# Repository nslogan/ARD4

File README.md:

# ARD4

## Description

Optically-isolated 4-channel automotive relay driver (ARD). Intended for use in lab environment, robust and flexible driver with 1A output possible per channel. Jumper to select between active-high and active-low inputs, jumper to select between DB9 or external power for input side. Reverse-protection on both logic and relay side power. LED across relay driver output indicates if **relay** is getting power. Test points for logic and relay power, as well as one per channel on logic side. Board fits Sick of Beige DP8049 form factor (but should be used with 10mm stand-offs between board and top panel). You can find [this project on GitHub](https://github.com/nslogan/ARD4).

## Production

The board measures 3.15"x1.93" (80.01x49.02 mm) and was designed for production at [OSH Park](https://www.oshpark.com/). The OSHPark DRU is located in the `res/` folder.

The boards can be purchased [here](https://www.oshpark.com/shared_projects/R0TELkwq) @ $30.35 for three.

## Parts

All parts on this board are from the [LoganSmith-Eagle-Library](https://github.com/nslogan/LoganSmith-Eagle-Library) available on GitHub (work in progress).

The BOM is located in the release folder, all parts are sourced from Digi-Key.

## Project Structure

This project adheres to this structure:

	[ProjectName]
		README.md
		[release]
			[Major.Minor]
				ProjectName_BOM_Major.Minor.xls or ProjectName_BOM_BOM_Major.Minor.csv
				ProjectName_schematic_Major.Minor.pdf
				ProjectName_board-<top/mid#/bottom>_Major.Minor.png
				ProjectName_Major.Minor.sch
				ProjectName_Major.Minor.brd
				[Gerbers]
					...
			...
		[src]
			[Major.0]
				BoardName.sch
				BoardName.brd
				BOM.xls or BOM.csv
			[Major+1.0]
				...
			...
		[lib]
			...
		[res]
			Manufacturer.dru
			Manufacturer.cam

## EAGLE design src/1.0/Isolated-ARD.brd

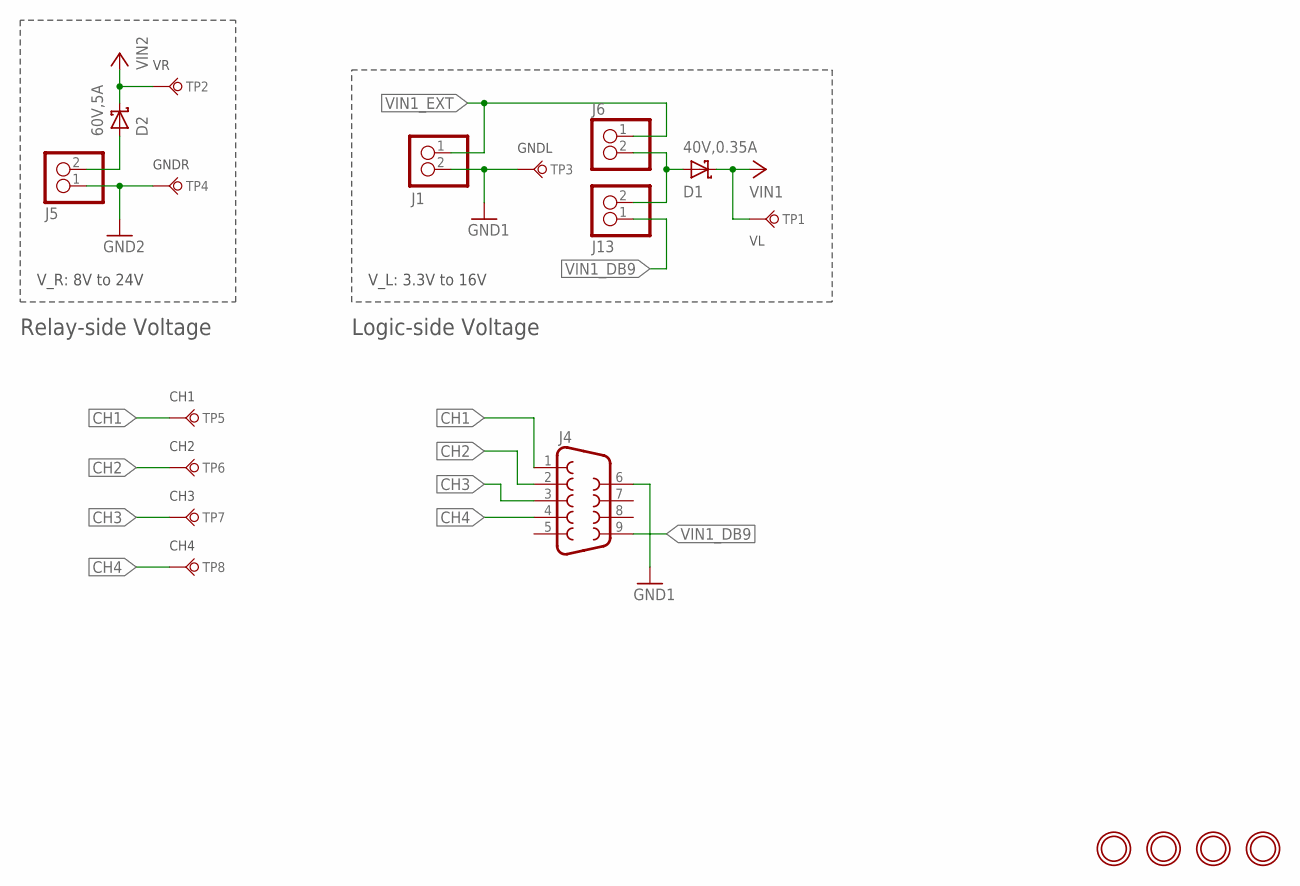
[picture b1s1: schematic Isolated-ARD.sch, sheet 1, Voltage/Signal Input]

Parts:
D1: 40V,0.35A; SOD-323
D2: 60V,5A; SMC-DIODE
J1, J5: M02SKT-3.5MM-R90; SOCKET-3.5MM-2-R90
J4: DB9-R90-F; DB9-R90
J6, J13: M02SQ1; 1X02_SQ1
TP1, TP2: TP-THRU-R; TP_THRU_CIRC
TP3, TP4, TP5, TP6, TP7, TP8: TP-THRU-B; TP_THRU_CIRC
U$13, U$14, U$15, U$21: MNTHOLE-M3; MNTHOLE_M3_PLATED

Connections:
CH1: J4.1, TP5.TP; also elsewhere on the board
CH2: J4.2, TP6.TP; also elsewhere on the board
CH3: J4.3, TP7.TP; also elsewhere on the board
CH4: J4.4, TP8.TP; also elsewhere on the board
GND1: J1.2, J4.6, TP3.TP; also elsewhere on the board
GND2: J5.1, TP4.TP; also elsewhere on the board
unnamed: D1.A, J6.2, J13.2
VIN1: D1.C, TP1.TP; also elsewhere on the board
VIN1_DB9: J4.9, J13.1
VIN1_EXT: J1.1, J6.1
VIN2: D2.C, TP2.TP; also elsewhere on the board
VIN2_EXT: D2.A, J5.2

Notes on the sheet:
V_L: 3.3V to 16V
V_R: 8V to 24V
Logic-side Voltage
Relay-side Voltage

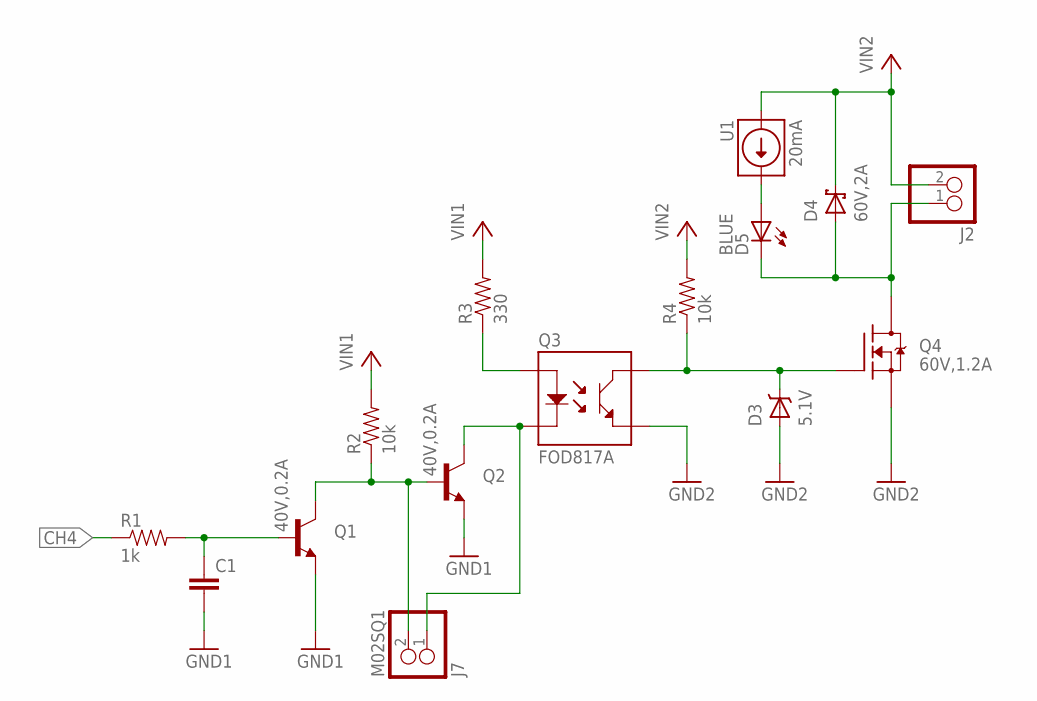
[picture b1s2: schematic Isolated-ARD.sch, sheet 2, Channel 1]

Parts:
C1: C-0805; 0805-CAP
D3: 5.1V; SOD-123
D4: 60V,2A; SMA-DIODE
D5: BLUE; 1206-LED; MPN LTST-C150KBKT; DIGIKEY_OC 160-1643-1-ND
J2: M02SKT-3.5MM-R90; SOCKET-3.5MM-2-R90
J7: M02SQ1; 1X02_SQ1
Q1, Q2: 40V,0.2A; SOT23-3
Q3: FOD817A; 4-SMD
Q4: 60V,1.2A; SOT23-3
R1: 1k; 0805-RES
R2: 10k; 0805-RES
R3: 330; 0805-RES
R4: 10k; 0805-RES; MPN ERJ-6GEYJ103V; DIGIKEY_OC P10KACT-ND
U1: 20mA; SOD-123

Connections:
CH4: R1.P$1 (1); also elsewhere on the board
GND1: C1.P$2 (2), Q1.2 (E), Q2.2 (E); also elsewhere on the board
GND2: D3.A, Q3.3 (T_E), Q4.2 (S); also elsewhere on the board
unnamed: J7.2, Q1.3 (C), Q2.1 (B), R2.P$1 (1)
unnamed: J7.1, Q2.3 (C), Q3.2 (LED_C)
unnamed: Q3.1 (LED_A), R3.P$1 (1)
unnamed: C1.P$1 (1), Q1.1 (B), R1.P$2 (2)
unnamed: D3.C, Q3.4 (T_C), Q4.1 (G), R4.P$1 (1)
unnamed: D4.A, D5.C, J2.1, Q4.3 (D)
unnamed: D5.A, U1.C
VIN1: R2.P$2 (2), R3.P$2 (2); also elsewhere on the board
VIN2: D4.C, J2.2, R4.P$2 (2), U1.A; also elsewhere on the board

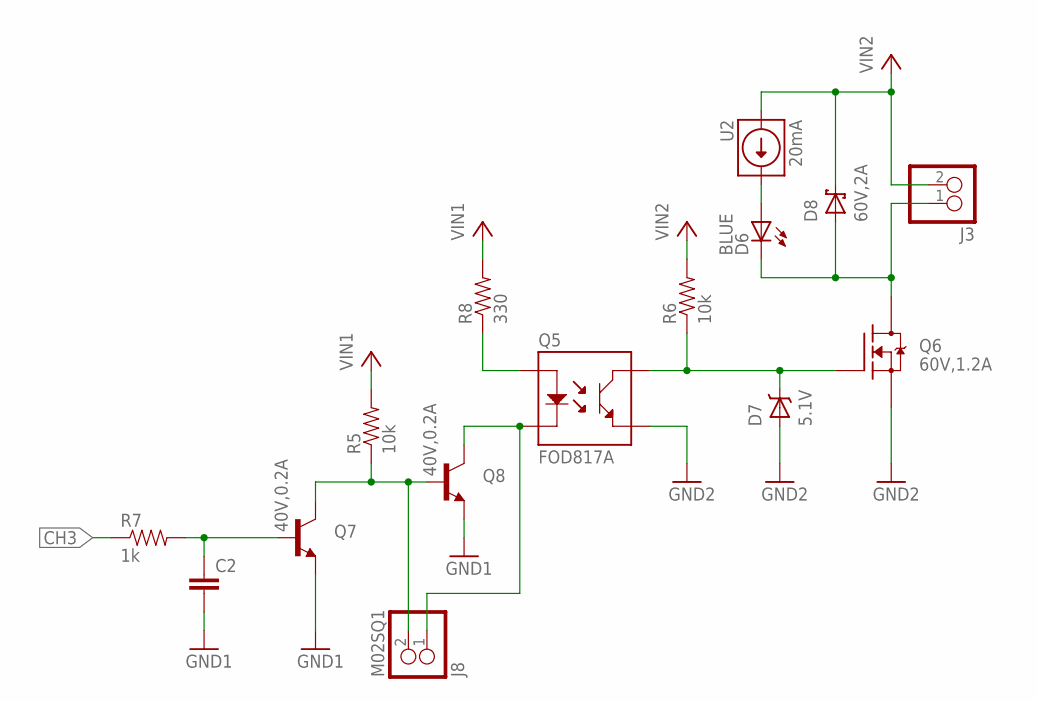
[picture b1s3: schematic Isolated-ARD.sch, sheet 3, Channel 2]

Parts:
C2: C-0805; 0805-CAP
D6: BLUE; 1206-LED; MPN LTST-C150KBKT; DIGIKEY_OC 160-1643-1-ND
D7: 5.1V; SOD-123
D8: 60V,2A; SMA-DIODE
J3: M02SKT-3.5MM-R90; SOCKET-3.5MM-2-R90
J8: M02SQ1; 1X02_SQ1
Q5: FOD817A; 4-SMD
Q6: 60V,1.2A; SOT23-3
Q7, Q8: 40V,0.2A; SOT23-3
R5: 10k; 0805-RES
R6: 10k; 0805-RES; MPN ERJ-6GEYJ103V; DIGIKEY_OC P10KACT-ND
R7: 1k; 0805-RES
R8: 330; 0805-RES
U2: 20mA; SOD-123

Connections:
CH3: R7.P$1 (1); also elsewhere on the board
GND1: C2.P$2 (2), Q7.2 (E), Q8.2 (E); also elsewhere on the board
GND2: D7.A, Q5.3 (T_E), Q6.2 (S); also elsewhere on the board
unnamed: J8.1, Q5.2 (LED_C), Q8.3 (C)
unnamed: Q5.1 (LED_A), R8.P$1 (1)
unnamed: D7.C, Q5.4 (T_C), Q6.1 (G), R6.P$1 (1)
unnamed: J8.2, Q7.3 (C), Q8.1 (B), R5.P$1 (1)
unnamed: C2.P$1 (1), Q7.1 (B), R7.P$2 (2)
unnamed: D6.C, D8.A, J3.1, Q6.3 (D)
unnamed: D6.A, U2.C
VIN1: R5.P$2 (2), R8.P$2 (2); also elsewhere on the board
VIN2: D8.C, J3.2, R6.P$2 (2), U2.A; also elsewhere on the board

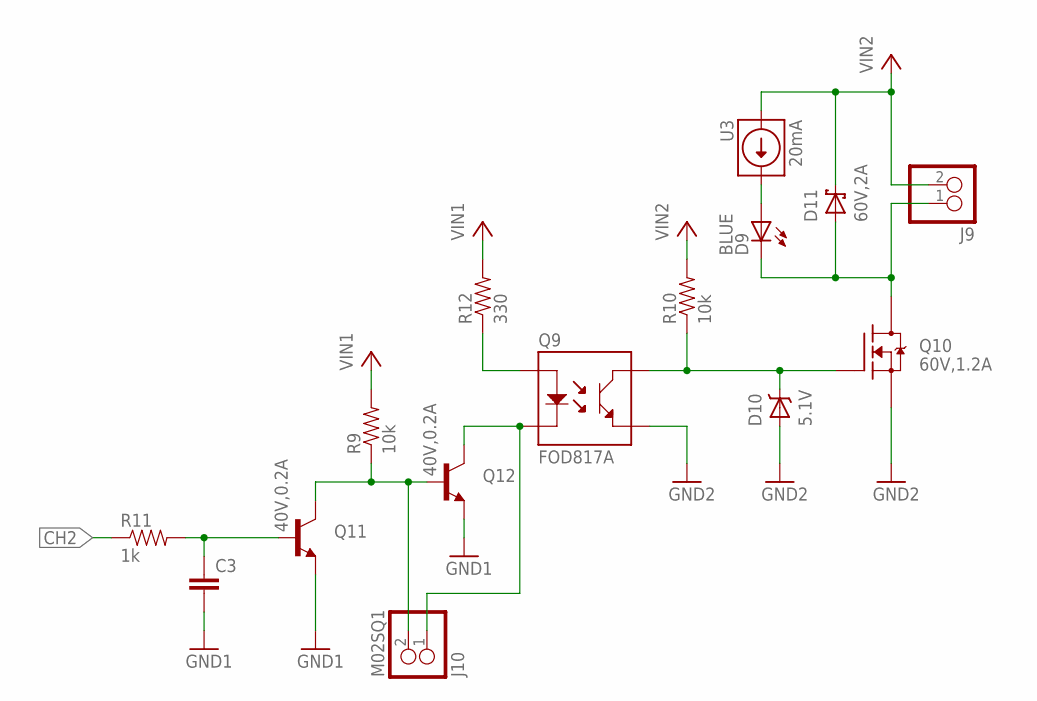
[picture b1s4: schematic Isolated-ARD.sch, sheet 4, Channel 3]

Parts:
C3: C-0805; 0805-CAP
D9: BLUE; 1206-LED; MPN LTST-C150KBKT; DIGIKEY_OC 160-1643-1-ND
D10: 5.1V; SOD-123
D11: 60V,2A; SMA-DIODE
J9: M02SKT-3.5MM-R90; SOCKET-3.5MM-2-R90
J10: M02SQ1; 1X02_SQ1
Q9: FOD817A; 4-SMD
Q10: 60V,1.2A; SOT23-3
Q11, Q12: 40V,0.2A; SOT23-3
R9: 10k; 0805-RES
R10: 10k; 0805-RES; MPN ERJ-6GEYJ103V; DIGIKEY_OC P10KACT-ND
R11: 1k; 0805-RES
R12: 330; 0805-RES
U3: 20mA; SOD-123

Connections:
CH2: R11.P$1 (1); also elsewhere on the board
GND1: C3.P$2 (2), Q11.2 (E), Q12.2 (E); also elsewhere on the board
GND2: D10.A, Q9.3 (T_E), Q10.2 (S); also elsewhere on the board
unnamed: J10.1, Q9.2 (LED_C), Q12.3 (C)
unnamed: Q9.1 (LED_A), R12.P$1 (1)
unnamed: D10.C, Q9.4 (T_C), Q10.1 (G), R10.P$1 (1)
unnamed: J10.2, Q11.3 (C), Q12.1 (B), R9.P$1 (1)
unnamed: C3.P$1 (1), Q11.1 (B), R11.P$2 (2)
unnamed: D9.C, D11.A, J9.1, Q10.3 (D)
unnamed: D9.A, U3.C
VIN1: R9.P$2 (2), R12.P$2 (2); also elsewhere on the board
VIN2: D11.C, J9.2, R10.P$2 (2), U3.A; also elsewhere on the board

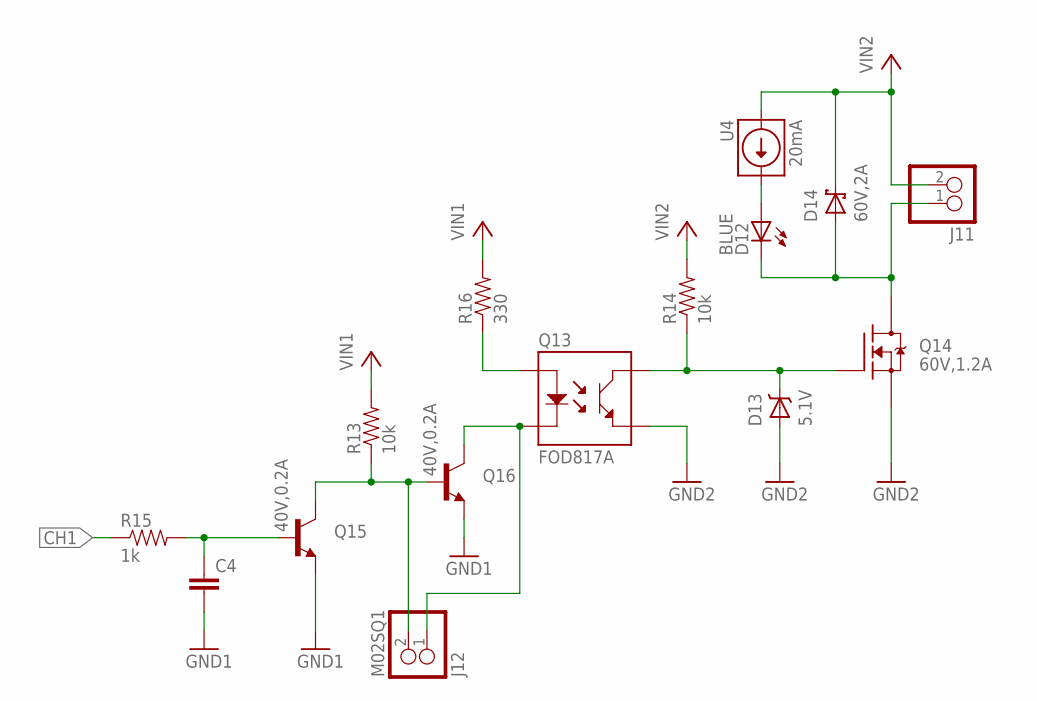
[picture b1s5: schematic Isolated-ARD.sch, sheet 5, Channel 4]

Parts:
C4: C-0805; 0805-CAP
D12: BLUE; 1206-LED; MPN LTST-C150KBKT; DIGIKEY_OC 160-1643-1-ND
D13: 5.1V; SOD-123
D14: 60V,2A; SMA-DIODE
J11: M02SKT-3.5MM-R90; SOCKET-3.5MM-2-R90
J12: M02SQ1; 1X02_SQ1
Q13: FOD817A; 4-SMD
Q14: 60V,1.2A; SOT23-3
Q15, Q16: 40V,0.2A; SOT23-3
R13: 10k; 0805-RES
R14: 10k; 0805-RES; MPN ERJ-6GEYJ103V; DIGIKEY_OC P10KACT-ND
R15: 1k; 0805-RES
R16: 330; 0805-RES
U4: 20mA; SOD-123

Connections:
CH1: R15.P$1 (1); also elsewhere on the board
GND1: C4.P$2 (2), Q15.2 (E), Q16.2 (E); also elsewhere on the board
GND2: D13.A, Q13.3 (T_E), Q14.2 (S); also elsewhere on the board
unnamed: J12.1, Q13.2 (LED_C), Q16.3 (C)
unnamed: Q13.1 (LED_A), R16.P$1 (1)
unnamed: D13.C, Q13.4 (T_C), Q14.1 (G), R14.P$1 (1)
unnamed: J12.2, Q15.3 (C), Q16.1 (B), R13.P$1 (1)
unnamed: C4.P$1 (1), Q15.1 (B), R15.P$2 (2)
unnamed: D12.C, D14.A, J11.1, Q14.3 (D)
unnamed: D12.A, U4.C
VIN1: R13.P$2 (2), R16.P$2 (2); also elsewhere on the board
VIN2: D14.C, J11.2, R14.P$2 (2), U4.A; also elsewhere on the board

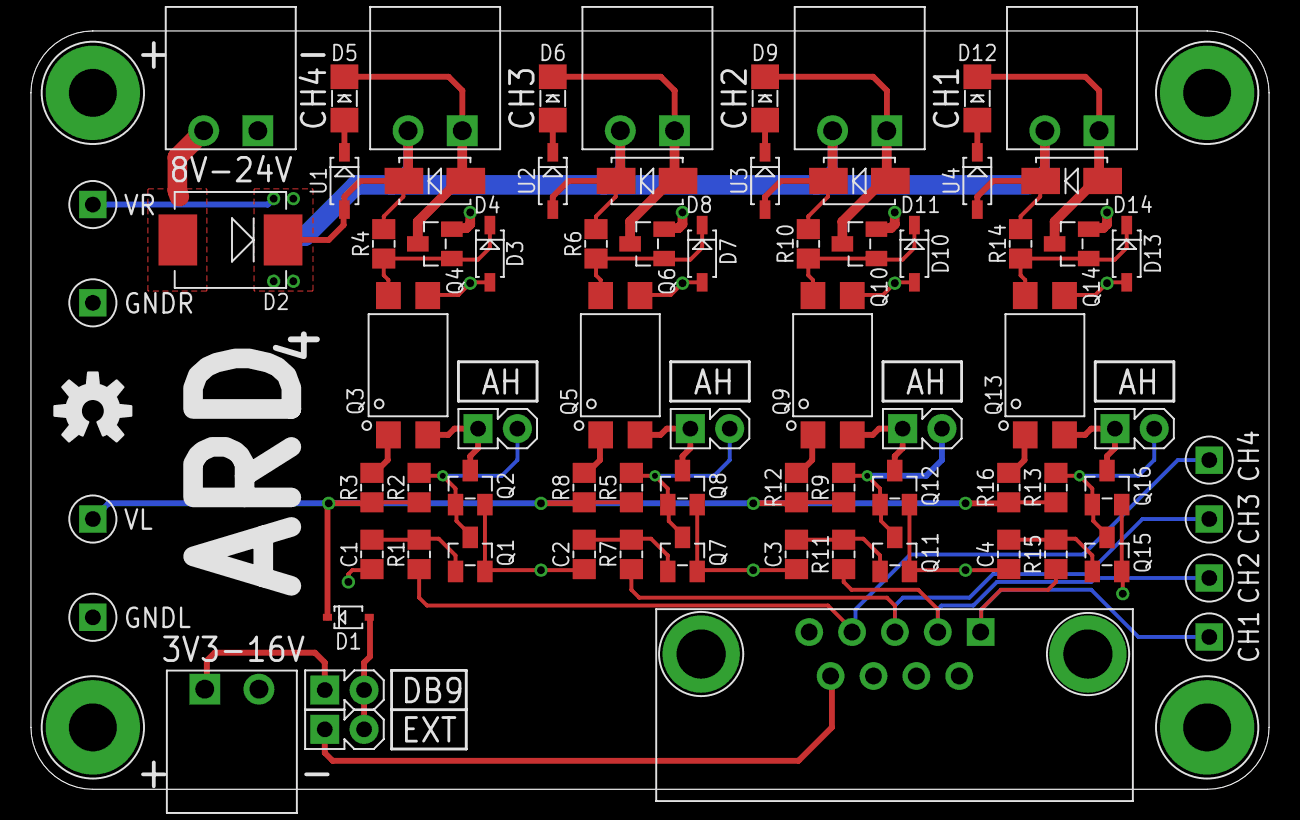
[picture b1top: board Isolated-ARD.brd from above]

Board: 2 copper layers, 80.0 x 49.0 mm, 81 parts (0 on the bottom side), 40 nets.

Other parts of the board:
U$12: DP8049_V1_PLATED
U$16: OSHW-LOGO-M

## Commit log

2014-10-31 Totally not the first commit and not done with layout...

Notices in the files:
parts and their libraries:
SparkFun-Aesthetics: Licensing: CC v3.0 Share-Alike You are welcome to use this library for commercial purposes.
